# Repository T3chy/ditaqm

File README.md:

# Do-it-Together Air Quality Measuring!

## Welcome!
Below are the links to all of the documents you need to get your very own distributed air quality sensor mesh set up!

# Paper Abstract
[Check it out!](ABSTRACT.pdf)

## Sensor Setup
- [ESP32](docs/esp32/) (the cool one)

- [Raspberry Pi](docs/raspi/)

## Web server / Database Setup

- [Spin up a dashboard for your data with POST endpoints for data collection!](docs/server.md)

- [Configure and host MySql database to store your data!](docs/db.md)

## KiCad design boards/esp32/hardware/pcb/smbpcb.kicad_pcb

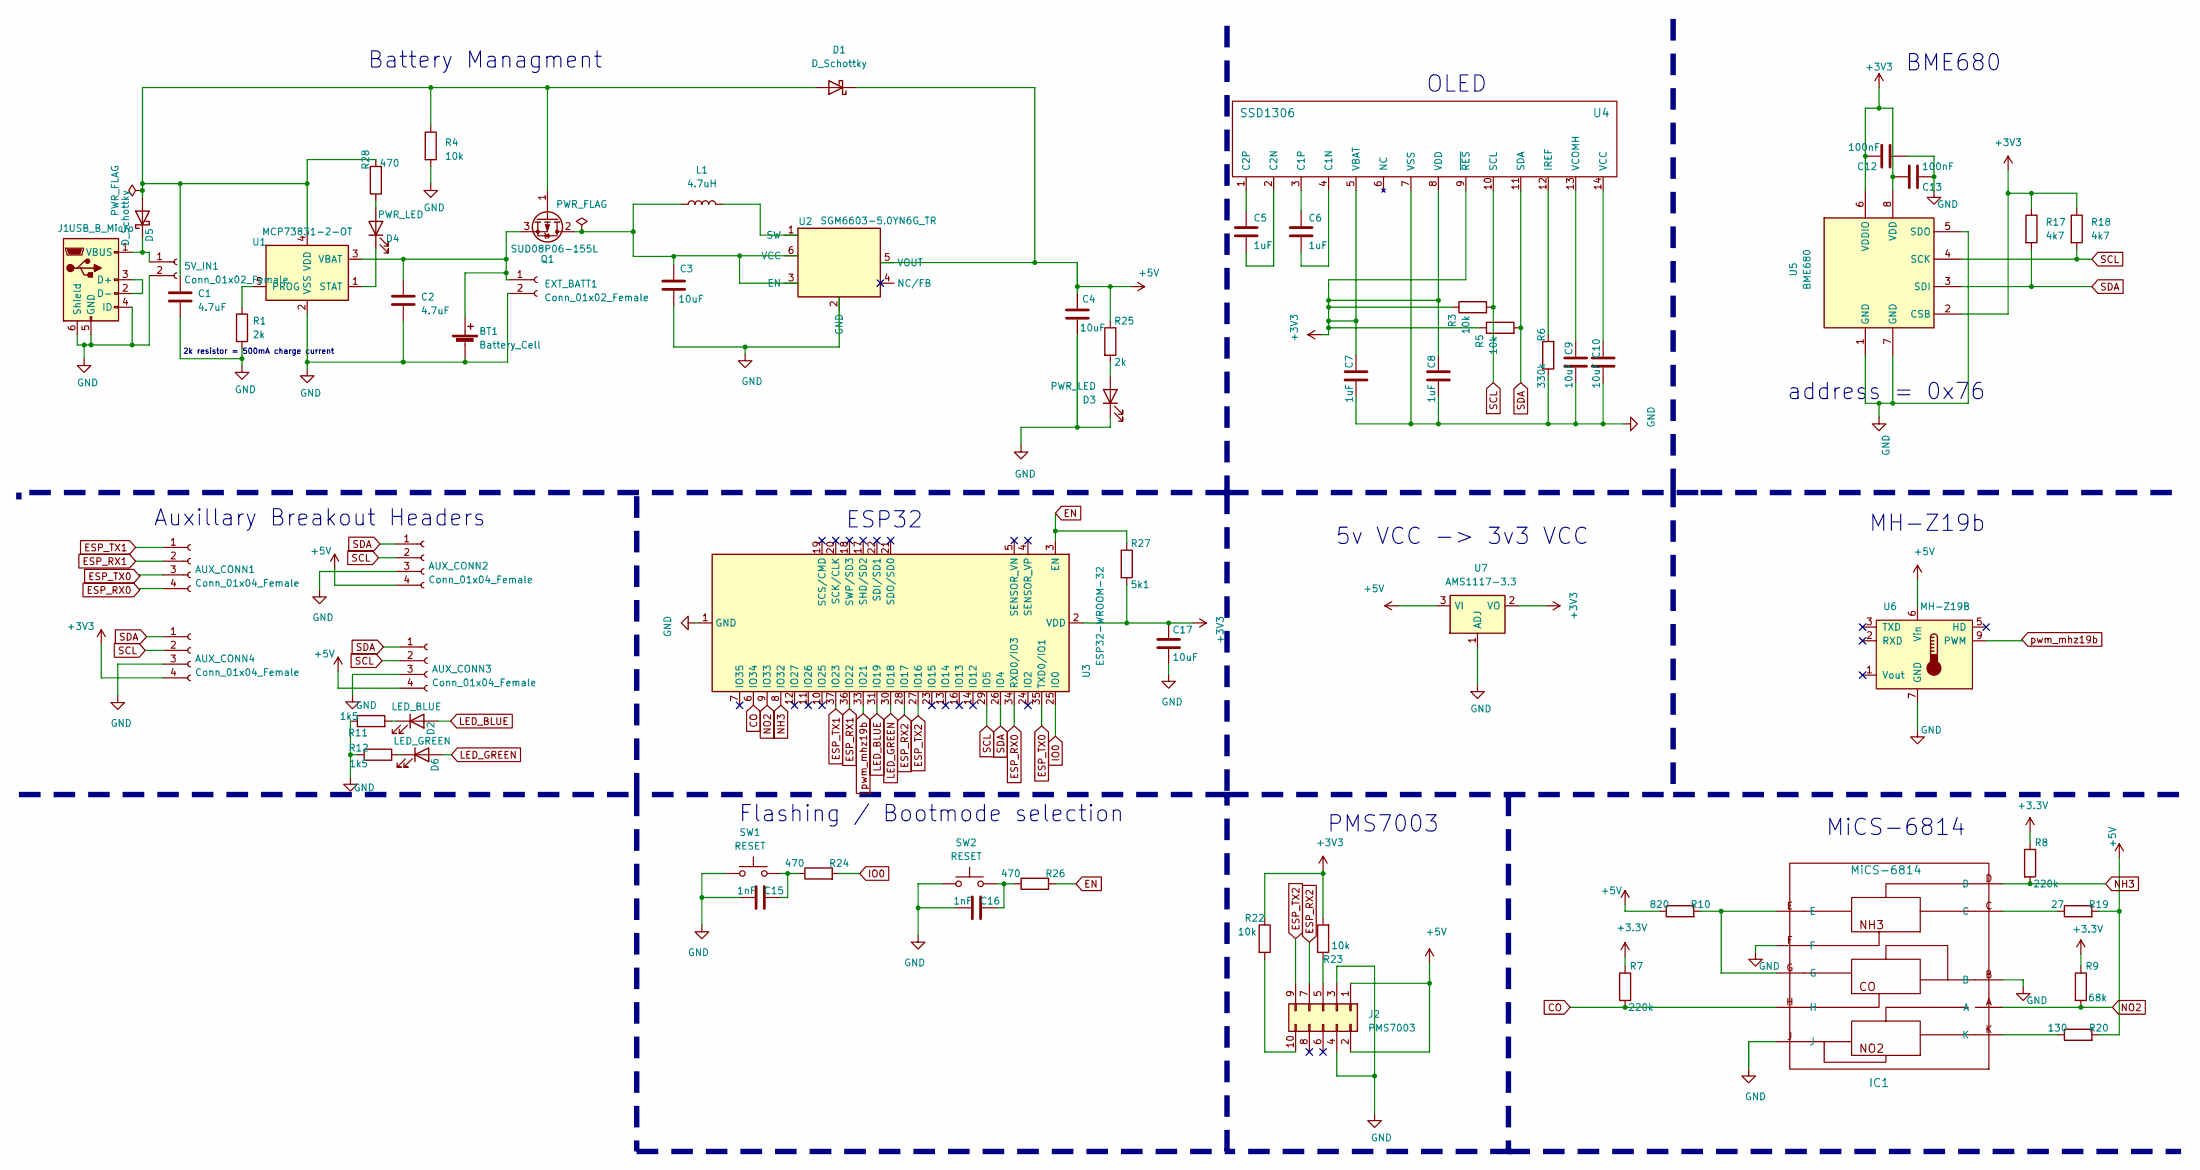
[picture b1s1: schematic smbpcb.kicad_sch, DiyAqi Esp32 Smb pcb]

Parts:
5V_IN1: Conn_01x02_Female; PinHeader_1x02_P2.54mm_Vertical; mfr_part_num C124375; LCSC C124375
AUX_CONN1, AUX_CONN2, AUX_CONN3, AUX_CONN4: Conn_01x04_Female; PinHeader_1x04_P2.54mm_Vertical; LCSC C124413
BT1: Battery_Cell; JST_EH_S2B-EH_1x02_P2.50mm_Horizontal; mfr_part_num A2501WR-2P; LCSC C225399
C1, C2: 4.7uF; C_1206_3216Metric; LCSC C412617
C3, C4: 10uF; C_1206_3216Metric; LCSC C92797
C5, C6, C7, C8: 1uF; C_0805_2012Metric; LCSC C28323
C9, C10, C17: 10uF; C_0805_2012Metric; mfr_part_num oops ordered this in 0805; LCSC C40894
C12, C13: 100nF; C_0805_2012Metric; LCSC C495959
C15, C16: 1nF; C_0805_2012Metric; LCSC C309046
D1, D5: D_Schottky; D_SOD-123; LCSC C8598
D2: LED_BLUE; C_0805_2012Metric; LCSC C192320
D3, D4: PWR_LED; LED_0805_2012Metric; LCSC C72037
D6: LED_GREEN; C_0805_2012Metric; LCSC C440522
EXT_BATT1: Conn_01x02_Female; PinHeader_1x02_P2.54mm_Vertical; LCSC C124375
IC1: MiCS-6814; SENSOR_MICS-6814; mfr_part_num MICS-6814; Mouser 523-MICS-6814
J1: USB_B_Micro; USB_Micro-B_Molex-105017-0001; mfr_part_num MicroXNJ; LCSC C404969
J2: PMS7003; mfr_part_num PMS7003; LCSC C84815
L1: 4.7uH; C_0805_2012Metric; LCSC C479902
Q1: SUD08P06-155L; TO-252-2; LCSC C558294
R1, R25: 2k; C_0805_2012Metric; LCSC C328391
R3, R4, R5, R22, R23: 10k; C_0805_2012Metric; LCSC C269724
R6: 330k; C_0805_2012Metric; LCSC C328392
R7, R8: 220k; C_0805_2012Metric; LCSC C294696
R9: 68k; C_0805_2012Metric; LCSC C445663
R10: 820; C_0805_2012Metric; LCSC C352174
R11, R12: 1k5; C_0805_2012Metric; LCSC C203762
R17, R18: 4k7; C_0805_2012Metric; LCSC C269733
R19: 27; C_0805_2012Metric; LCSC C104178
R20: 130; C_0805_2012Metric; LCSC C17451
R24, R26, R28: 470; C_0805_2012Metric; LCSC C136570
R27: 5k1; C_0805_2012Metric; LCSC C328405
SW1, SW2: RESET; SW_SPST_Omron_B3FS-101xP; LCSC C589246
U1: MCP73831-2-OT; SOT-23-5; LCSC C424093
U2: SGM6603-5.0YN6G_TR; SOT-23-6; LCSC C79689
U3: ESP32-WROOM-32; LCSC C82899
U4: SSD1306; SSD1306_OLED-0.91-128x32; mfr_part_num QG-2832TLBFG02; LCSC C91220
U5: BME680; Bosch_LGA-8_3x3mm_P0.8mm_ClockwisePinNumbering; mfr_part_num BME680; LCSC C125972
U6: MH-Z19B; Winsen_MH-Z19B; mfr_part_num MH-Z19B; LCSC C242514
U7: AMS1117-3.3; SOT-223-3_TabPin2; mfr_part_num AMS1117-3.3; LCSC C369933

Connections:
+5V: AUX_CONN2.4, AUX_CONN3.4, C4.1, D1.1 (K), J2.1, J2.2, R10.1, R19.2, R20.2, R25.1, U2.5 (VOUT), U6.6 (Vin), U7.3 (VI)
CO: IC1.H, R7.2, U3.6 (IO34)
EN: R26.2, R27.1, U3.3 (EN)
ESP_RX0: AUX_CONN1.4, U3.34 (RXD0/IO3)
ESP_RX1: AUX_CONN1.2, U3.36 (IO22)
ESP_RX2: J2.7, U3.28 (IO17)
ESP_TX0: AUX_CONN1.3, U3.35 (TXD0/IO1)
ESP_TX1: AUX_CONN1.1, U3.37 (IO23)
ESP_TX2: J2.9, U3.27 (IO16)
GND: 5V_IN1.2, AUX_CONN2.3, AUX_CONN3.3, AUX_CONN4.3, BT1.2 (-), C1.2, C2.2, C3.2, C4.2, C7.2, C8.2, C9.1, C10.1, C12.2, C13.1, C15.1, C16.1, C17.2, D3.1 (K), EXT_BATT1.2, IC1.B, IC1.F, IC1.J, J1.4 (ID), J1.5 (GND), J1.6 (Shield), J2.3, J2.4, R1.2, R4.2, R6.1, R11.1, R12.1, SW1.2, SW2.2, U1.2 (VSS), U2.2 (GND), U3.1 (GND), U3.15 (GND), U3.38 (GND), U3.39 (GND), U4.7 (VSS), U5.1 (GND), U5.5 (SDO), U5.7 (GND), U6.7 (GND), U7.1 (ADJ); also elsewhere on the board
IO0: R24.2, U3.25 (IO0)
LED_BLUE: D2.2 (A), U3.31 (IO19)
LED_GREEN: D6.2 (A), U3.30 (IO18)
NH3: IC1.D, R8.2, U3.8 (IO32)
NO2: IC1.A, R9.2, U3.9 (IO33)
unnamed: 5V_IN1.1, D5.1 (K), J1.1 (VBUS)
unnamed: BT1.1 (+), C2.1, EXT_BATT1.1, Q1.3 (S), U1.3 (VBAT)
unnamed: C1.1, D1.2 (A), D5.2 (A), Q1.1 (G), R4.1, R28.2, U1.4 (VDD)
unnamed: C3.1, L1.1, Q1.2 (D), U2.3 (EN), U2.6 (VCC)
unnamed: C5.1, U4.1 (C2P)
unnamed: C5.2, U4.2 (C2N)
unnamed: C6.1, U4.3 (C1P)
unnamed: C6.2, U4.4 (C1N)
unnamed: C9.2, U4.13 (VCOMH)
unnamed: C10.2, U4.14 (VCC)
unnamed: C15.2, R24.1, SW1.1
unnamed: C16.2, R26.1, SW2.1
unnamed: D2.1 (K), R11.2
unnamed: D3.2 (A), R25.2
unnamed: D4.1 (K), U1.1 (STAT)
unnamed: D4.2 (A), R28.1
unnamed: D6.1 (K), R12.2
unnamed: IC1.C, R19.1
unnamed: IC1.E, IC1.G, R10.2
unnamed: IC1.K, R20.1
unnamed: J1.2 (D-), J1.3 (D+)
unnamed: J2.5, R23.1
unnamed: J2.10, R22.2
unnamed: L1.2, U2.1 (SW)
unnamed: R1.1, U1.5 (PROG)
unnamed: R6.2, U4.12 (IREF)
SCL: AUX_CONN2.2, AUX_CONN3.2, AUX_CONN4.2, R3.2, R18.2, U3.29 (IO5), U4.10 (SCL), U5.4 (SCK)
SDA: AUX_CONN2.1, AUX_CONN3.1, AUX_CONN4.1, R5.2, R17.2, U3.26 (IO4), U4.11 (SDA), U5.3 (SDI)
pwm_mhz19b: U3.33 (IO21), U6.9 (PWM)

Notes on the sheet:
2k resistor = 500mA charge current
Auxillary Breakout Headers
Battery Managment
ESP32
Flashing / Bootmode selection
PMS7003
OLED
5v VCC -> 3v3 VCC
MiCS-6814
address = 0x76
MH-Z19b
BME680

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
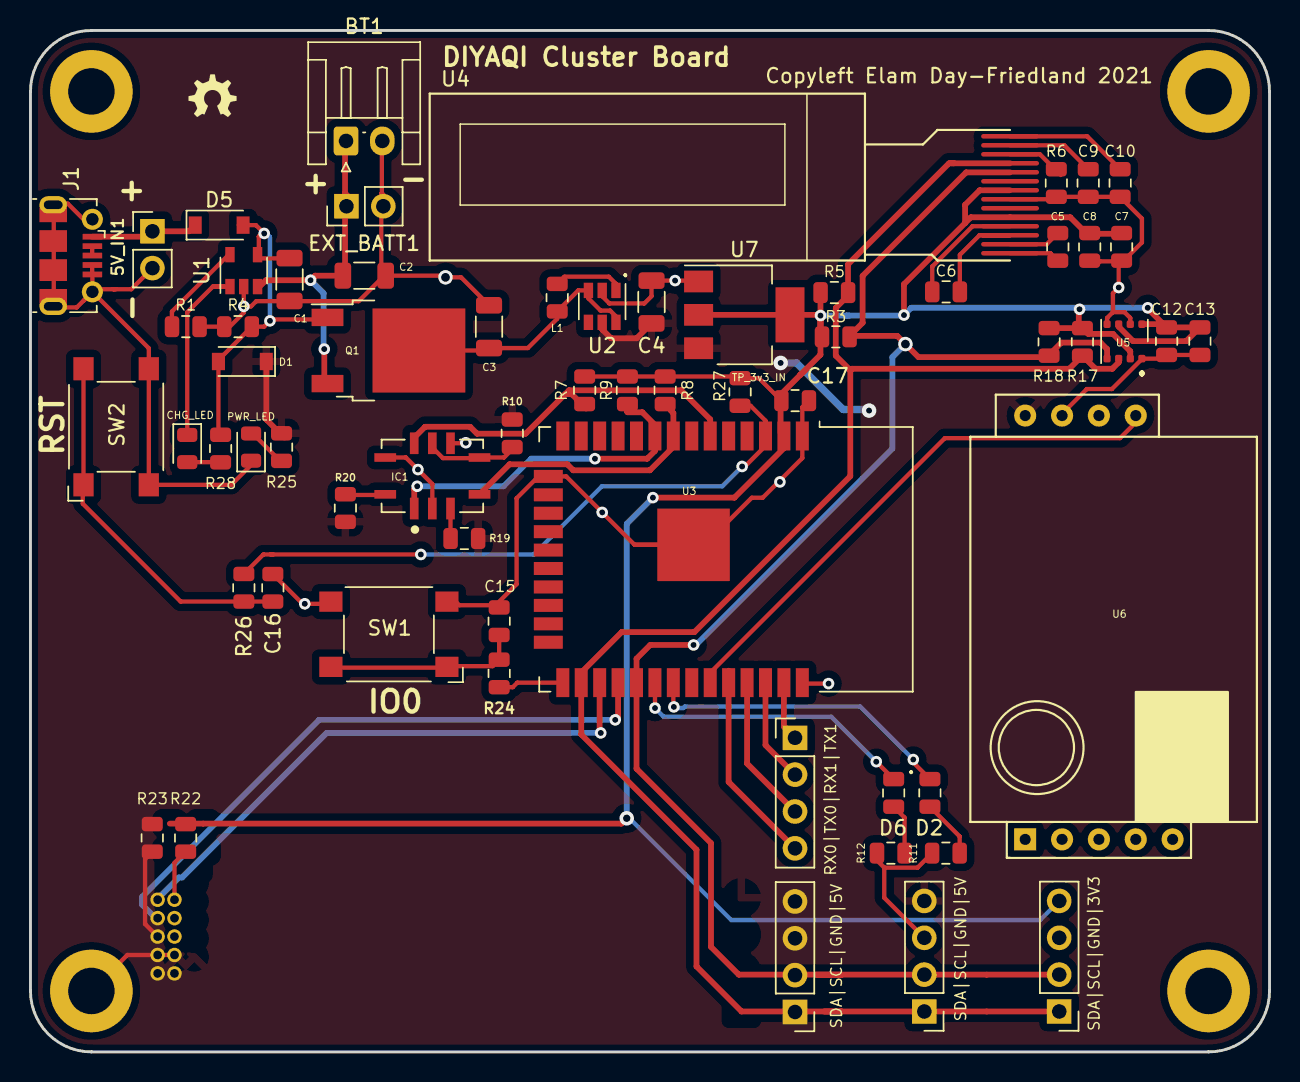
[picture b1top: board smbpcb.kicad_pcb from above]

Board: 2 copper layers, 85.4 x 70.4 mm, 65 parts (0 on the bottom side), 45 nets.

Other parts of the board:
MOUNT4: MountingHole_3.2mm_M3_ISO7380_Pad

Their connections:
GND: MOUNT4.1; also elsewhere on the board

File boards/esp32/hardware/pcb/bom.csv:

Reference, Quantity, Value, Footprint, Datasheet, LCSC, mfr_part_num, Mouser
EXT_BATT1 5V_IN1 ,2,"Conn_01x02_Female","Connector_PinHeader_2.54mm:PinHeader_1x02_P2.54mm_Vertical","~","C124375","C124375",""
AUX_CONN1 AUX_CONN2 AUX_CONN3 AUX_CONN4 ,4,"Conn_01x04_Female","Connector_PinHeader_2.54mm:PinHeader_1x04_P2.54mm_Vertical","~","C124413","C124413",""
BT1 ,1,"Battery_Cell","Connector_JST:JST_EH_S2B-EH_1x02_P2.50mm_Horizontal","~","C225399","A2501WR-2P",""
C1 C2 ,2,"4.7uF","Capacitor_SMD:C_1206_3216Metric","~","C412617",""," 963-UMJ316BC7475KLHT "
C12 C13 ,2,"100nF","Capacitor_SMD:C_0805_2012Metric","~","C495959","","C0805X104K101TB"
C15 C16 ,2,"1nF","Capacitor_SMD:C_0805_2012Metric","~","C309046","","TCC0805X7R102K501DTS"
C3 C4 ,2,"10uF","Capacitor_SMD:C_1206_3216Metric","","C92797 ",""," 963-UMJ316BC7475KLHT "
C5 C6 C7 C8 ,4,"1uF","Capacitor_SMD:C_0805_2012Metric","~","C28323",""," 187-CL21B105KBFNNNE "
C9 C10 C17 ,3,"10uF","Capacitor_SMD:C_0805_2012Metric","~"," C40894 ","oops ordered this in 0805","0805X106K250NT"
D1 D5 ,2,"D_Schottky","Diode_SMD:D_SOD-123","~","C8598",""," 833-B5819W-TP "
D2 ,1,"LED_BLUE","Capacitor_SMD:C_0805_2012Metric","~"," C192320 ","","TJ-S2012SW8TGLC6B-A5"
D3 D4 ,2,"PWR_LED","LED_SMD:LED_0805_2012Metric","~","C72037",""," 755-SML-H12U8TT86C "
D6 ,1,"LED_GREEN","Capacitor_SMD:C_0805_2012Metric","~","C440522","","TJ-S2012CY8T5ALC2G-A5"
J1 ,1,"USB_B_Micro","Connector_USB:USB_Micro-B_Molex-105017-0001","~","C404969","MicroXNJ",""
J2 ,1,"PMS7003","mics:PMS7003","https://www.espruino.com/datasheets/PMS7003.pdf","C84815 ","PMS7003",""
L1 ,1,"4.7uH","Capacitor_SMD:C_0805_2012Metric","~","C479902 ","","SCMI201209U4R7KT"
Q1 ,1,"SUD08P06-155L","Package_TO_SOT_SMD:TO-252-2","https://www.vishay.com/docs/62843/sud08p06-155l-ge3.pdf","C558294",""," 781-SUD08P06-155L-E3 "
R1 R25 ,2,"2k","Capacitor_SMD:C_0805_2012Metric","~","C328391","","AECR0805F2K00K9"
R10 ,1,"820","Capacitor_SMD:C_0805_2012Metric","~","C352174","","AECR0805F820RK9"
R11 R12 ,2,"1k5","","~"
R17 R18 ,2,"4.7k","Capacitor_SMD:C_0805_2012Metric","~","C269733","","RMC08054.7K5%N"
R19 ,1,"27","Capacitor_SMD:C_0805_2012Metric","~","C104178","","RTT0527R0FTP"
R2 R3 R4 R5 R22 R23 ,6,"10k","Capacitor_SMD:C_0805_2012Metric","~","C269724",""," 71-TNPU080510K0AWEN "
R20 ,1,"130","Capacitor_SMD:C_0805_2012Metric","~"," C17451 ","","CR0805-FX-1300ELF"
R24 R26 R28 ,3,"470","Capacitor_SMD:C_0805_2012Metric","~","C136570","","RS-05K4700FT"
R27 ,1,"5.1k","Capacitor_SMD:C_0805_2012Metric","~","C328405",""," 71-CRCW06035K10FKEAC "
R6 ,1,"330k","Capacitor_SMD:C_0805_2012Metric","~"," C328392 ","","AECR0805F330KK9"
R7 R8 ,2,"220k","Capacitor_SMD:C_0805_2012Metric","~","C294696 ","","RS-05K224JT"
R9 ,1,"68k","Capacitor_SMD:C_0805_2012Metric","~","C445663 ","","ERA6AEB683V"
SW1 SW2 ,2,"RESET","Button_Switch_SMD:SW_SPST_Omron_B3FS-101xP","~","C589246","","ST-1102W-4.3"
U1 ,1,"MCP73831-2-OT","Package_TO_SOT_SMD:SOT-23-5","http://ww1.microchip.com/downloads/en/DeviceDoc/20001984g.pdf","C424093",""," 579-MCP73831T-2ACIOT "
U2 ,1,"SGM6603-5.0YN6G_TR","Package_TO_SOT_SMD:SOT-23-6","https://www.analog.com/media/en/technical-documentation/data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","C79689","","SGM6603-5.0YN6G/TR"
U3 ,1,"ESP32-WROOM-32","RF_Module:ESP32-WROOM-32","https://www.espressif.com/sites/default/files/documentation/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","C82899",""," 356-ESPWROOM3216MB "
U4 ,1,"SSD1306","stuff:SSD1306_OLED-0.91-128x32","https://datasheet.lcsc.com/szlcsc/1809291515_Shenzhen-Allvis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","C91220","QG-2832TLBFG02",""
U5 ,1,"BME680","Package_LGA:Bosch_LGA-8_3x3mm_P0.8mm_ClockwisePinNumbering","https://ae-bst.resource.bosch.com/media/_tech/media/datashee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","C125972","BME680"," 262-BME680 "
U7 ,1,"AMS1117-3.3","Package_TO_SOT_SMD:SOT-223-3_TabPin2","http://www.advanced-monolithic.com/pdf/ds1117.pdf","C369933","AMS1117-3.3"," 595-REG1117-3.3/2K5 "

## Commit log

2021-01-19 fixed order
2021-01-19 making tests
2021-01-20 now parses multiple sensors from config
2021-01-20 tests
2021-01-20 multi sensor POSTing baby
2021-01-20 oops
2021-01-20 forgot to update sensor message
2021-01-20 reword
2021-01-20 forgot to take out a cd
2021-01-20 func misspell
2021-01-20 oops p2
2021-01-20 why am I this dumb
2021-01-20 BRUH
2021-01-20 fixed a bad part
2021-01-20 whoops forgot name key
2021-01-21 added schematics
2021-01-21 hopefully more PEP-8-y
2021-01-21 hopefully more PEP-8-y (tests)
2021-01-21 everything is probably broken now... WIP
2021-01-21 IMPORTANT UPDATE PULL IMMEDIATELY
2021-01-21 added some comments
2021-01-21 more commenting and prettyifying
2021-01-21 better exception handling:
2021-01-21 refactor read_pwm
2021-01-21 prettier
2021-01-21 loose ends
2021-01-21 misnamed smth
2021-01-23 inital ESP8266 Support!
    this took 10 hours lmao
2021-01-23 slightly less broken probably make it read from a config file
2021-01-23 working
2021-01-23 better
2021-01-23 no more today
2021-01-24 learning experience in progress
2021-01-29 working pcb
2021-01-29 it begins
2021-01-29 probably not working but it's written
2021-01-29 pls do recheck sensors on boot
2021-01-29 semi
2021-01-29 double oops
2021-01-29 fixed anti-dupe for deps"
2021-01-29 fixed config read error
2021-01-29 below -> above
2021-01-30 fixed
2021-01-30 test this feature
2021-01-30 ok it workd
2021-01-30 reorganizing
2021-01-30 minor edits
2021-01-30 begining of sensor detection
2021-01-30 fixed some oopsies
2021-01-31 progress; untested"
2021-01-31 updates config at boot
2021-02-09 smt time
2021-02-09 pms7003 time
2021-02-09 more work'
2021-02-10 ordering dis
2021-02-10 frick
2021-02-10 AP init time baby
2021-02-10 initally working
2021-02-10 rudamentary persistence
2021-02-12 less broken
2021-02-13 more setup stuff Note: not putting everything in main because for some reason editing main is prohibited and I want to support OTA updates in the future maybe
2021-02-14 updated bom w mfr part nums
2021-02-14 added decoupling cap to 3v3 off of esp32 board
2021-02-15 merging
2021-02-15 ohl for the pcb stuff
2021-02-15 need to write req handlers
2021-02-16 added mouser part nums"
2021-02-16 updated bom
2021-02-18 oled time
2021-02-20 box time
2021-02-20 lid and rearranging
2021-02-20 made everything 0805 or bigger except that nagging BGA Linear regulator and the bme680
2021-02-21 made more parametric and added battery part
2021-02-21 fan time
2021-02-21 vent holes
2021-02-22 tidied up
2021-02-22 more tidying and controled impedence traces for important stuff
2021-02-22 assembly QOL improvements
2021-02-22 added dot for bme680
2021-02-22 these probbaly should have been 1 commit
2021-02-24 wrong micro usb footprint
2021-02-24 forgot to save
2021-02-25 v1 probably
2021-02-25 prettify
2021-02-25 added silkscreen stuff
2021-02-28 help
2021-03-01 printing these full scale
2021-03-01 printing'
2021-03-03 finally start of working config persistence paqst wifi'
2021-03-04 finally got the actual board in gonna use idf and just deploy firmwares cuz idk why but ampy and others don't work
2021-03-04 fixed tolerences for fan
2021-03-05 sensor reg kinda wokrs
2021-03-05 hopefully road to readability
2021-03-05 starting to make presentable
2021-03-05 ap working
2021-03-06 setup maybe done but untested so not
2021-03-07 woho setup at least showing up for now
2021-03-07 added multithreading for wan access
2021-03-07 sensor time
2021-03-07 untested hopefuilly epic tho
2021-03-08 switch footprints were wrong..."
2021-03-08 swapped header order to be more standard
2021-03-08 pulled up io0 instaed of en. dhmu
2021-03-08 turns out mhz19b uses 3v3 logic and also uart doesn't work
2021-03-09 starting to bring it all together
2021-03-10 autodetect confirmed working on pms and bme'
2021-03-10 mics still broken, sensors otherwise good
2021-03-12 maybe this will work need 2 test
2021-03-12 mics sucks lol
2021-03-12 everything but mics is working
2021-03-13 added some comments:
2021-03-13 bme tested and working gonna try others tonight'
2021-03-13 woot woot all 4 sensors work! (bme280)
2021-03-14 fixed mics pullups
2021-03-14 tidying
2021-03-16 moving stuff
2021-03-16 moving stuff around
2021-03-16 webstack docs
2021-03-16 added status leds
2021-03-16 led time
2021-03-16 autogenerated
2021-03-16 whoops
2021-03-16 it would be super cool if these messages were useful
2021-03-16 mad quirky
2021-03-16 moving license
2021-03-16 ok I think we're good
2021-03-16 little more legit
2021-03-19 updated abstract
2021-03-19 more detail
2021-03-20 adding stls too incase you don't want to download freecad
2021-03-20 changed some title block stuff
2021-03-20 better schematic
2021-03-20 enclosure prettificaiton
2021-03-20 more readable schematic
2021-03-21 gerbers n stuff
2021-03-21 starting real documentation
2021-03-21 went through DRC
2021-03-21 in case you're SUPER lazyu
2021-03-21 moved bom
2021-03-21 added bom to src zip
2021-04-01 added ordering instructions
2021-04-01 moved the note
2021-04-01 added important frustration-saver
2021-04-01 removed oled reset pullup it broke the oled
2021-04-01 minor stuff
2021-04-01 more minor stuff
2021-04-04 status leds! sequence is in for wifi at least using threads
2021-04-05 woho POSTinggit add .
2021-04-05 minor
2021-04-08 minor stupid stuff changed
2021-04-09 minor tweaks
2021-04-10 a little ftrimware stuff
2021-04-12 name change
2021-04-25 added compiled firmware

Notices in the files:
boards/esp32/hardware/pcb/smbpcb.kicad_pcb:
Copyleft Elam Day-Friedland 2021
